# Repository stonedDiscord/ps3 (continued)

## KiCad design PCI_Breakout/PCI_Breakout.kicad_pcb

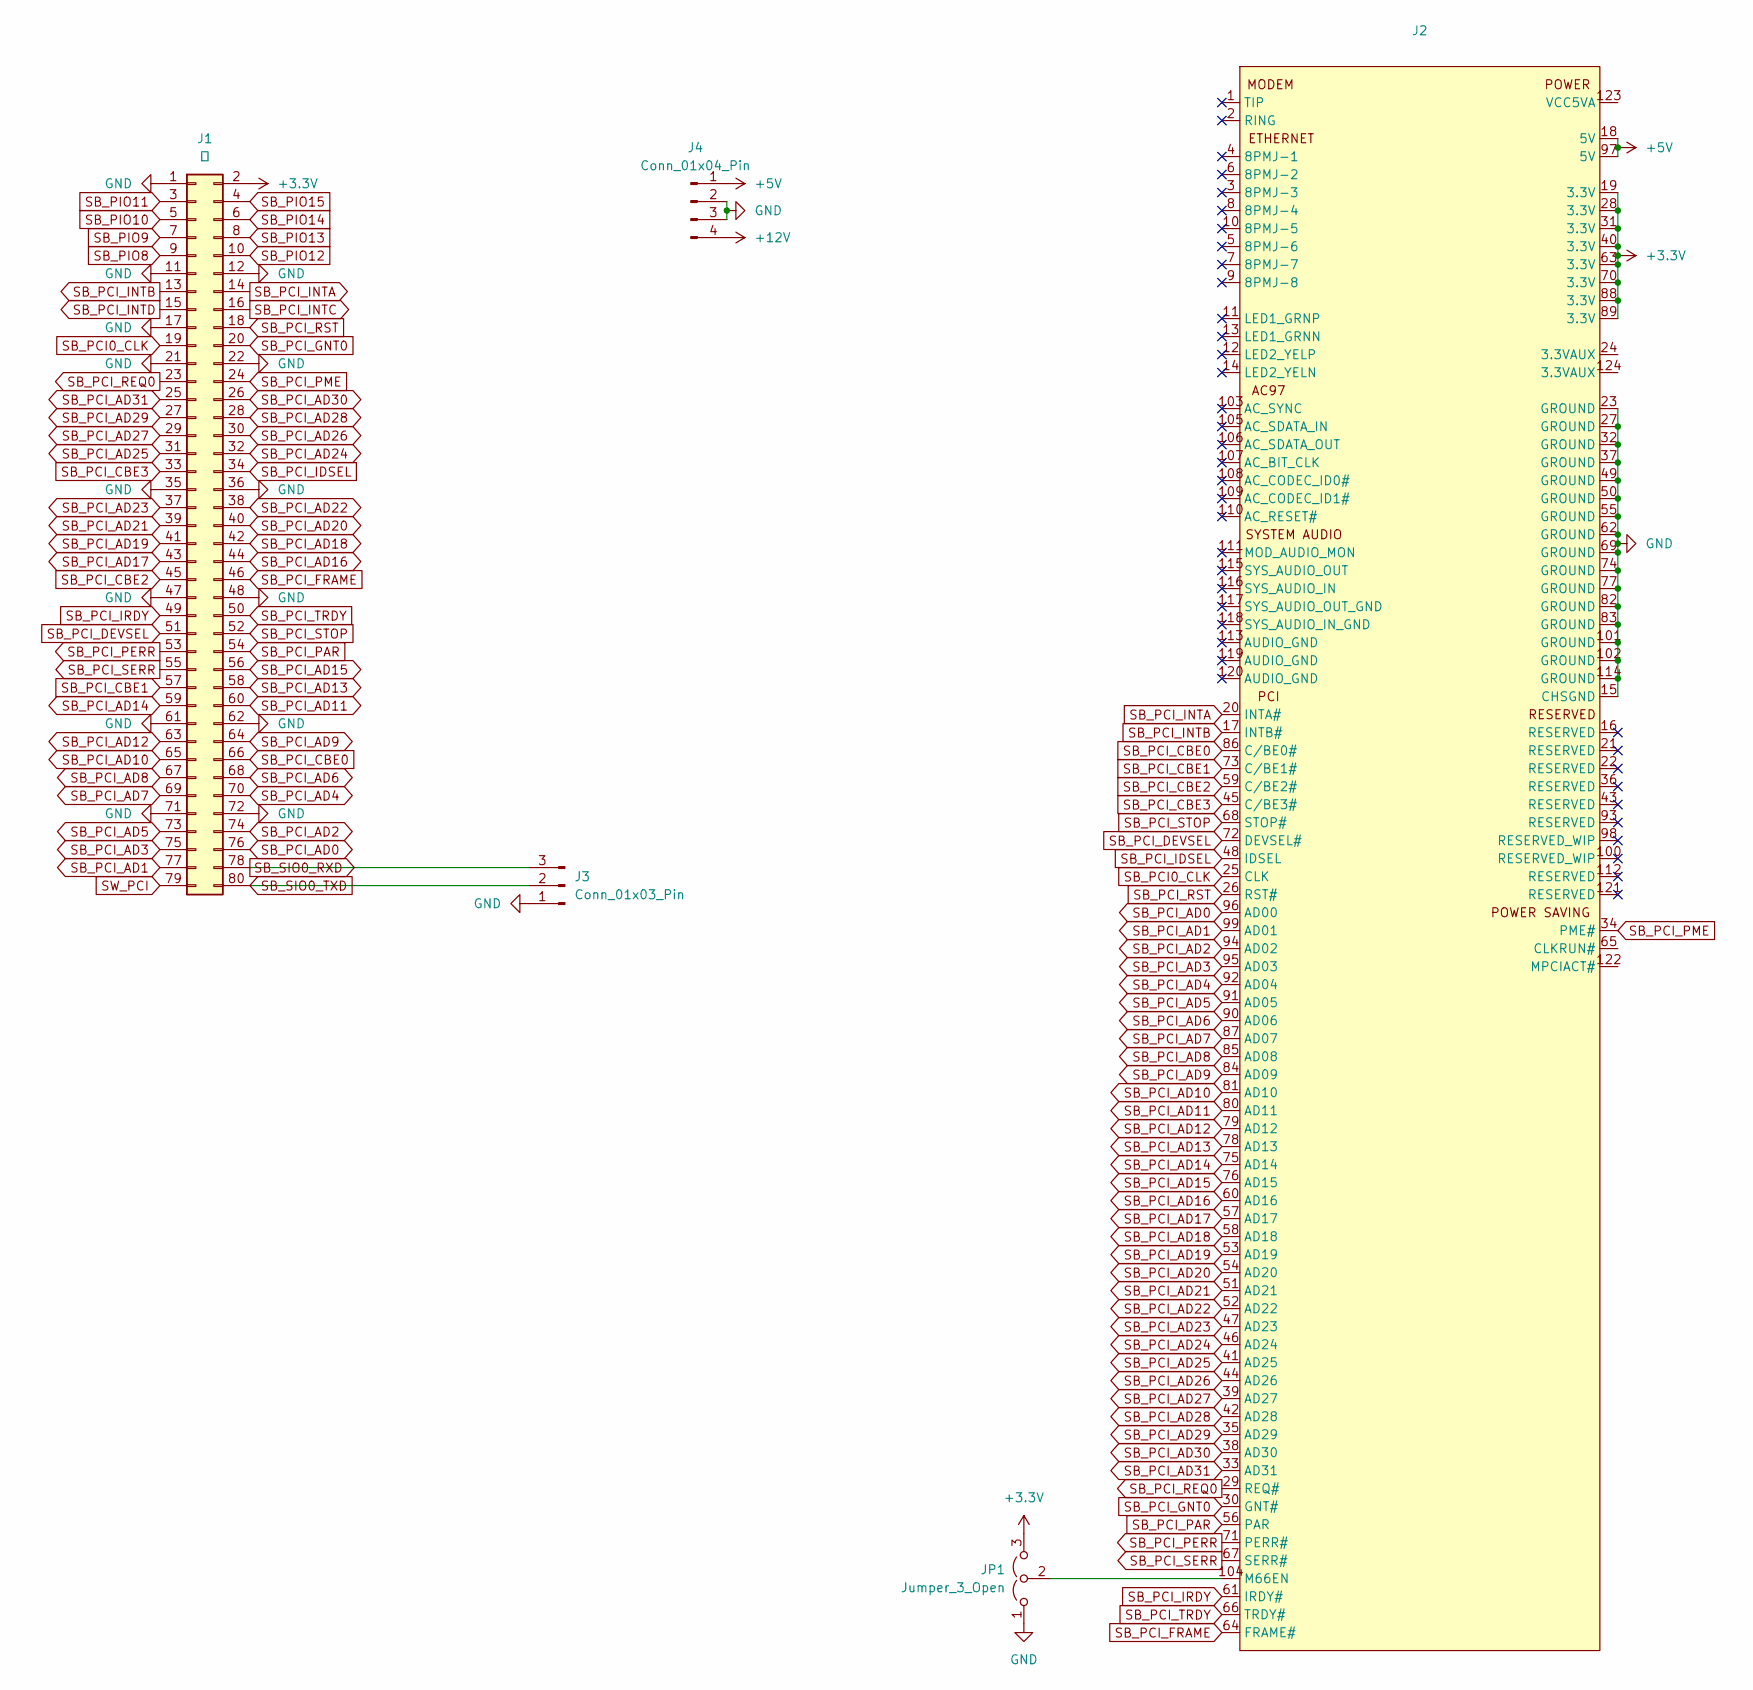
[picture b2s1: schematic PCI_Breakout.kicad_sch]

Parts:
J1: 凹; Molex_SlimStack_55560-0801_2x40_P0.50mm_Vertical
J2: 114B-40B00-R02
J3: Conn_01x03_Pin; PinHeader_1x03_P2.54mm_Vertical
J4: Conn_01x04_Pin; PinHeader_1x04_P2.54mm_Horizontal
JP1: Jumper_3_Open; SolderJumper-3_P2.0mm_Open_TrianglePad1.0x1.5mm

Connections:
+3.3V: J1.2, J2.19 (3.3V), J2.28 (3.3V), J2.31 (3.3V), J2.40 (3.3V), J2.63 (3.3V), J2.70 (3.3V), J2.88 (3.3V), J2.89 (3.3V), JP1.3 (B)
+5V: J2.18 (5V), J2.97 (5V), J4.1
+12V: J4.4
GND: J1.1, J1.11, J1.12, J1.17, J1.21, J1.22, J1.35, J1.36, J1.47, J1.48, J1.61, J1.62, J1.71, J1.72, J2.15 (CHSGND), J2.23 (GROUND), J2.27 (GROUND), J2.32 (GROUND), J2.37 (GROUND), J2.49 (GROUND), J2.50 (GROUND), J2.55 (GROUND), J2.62 (GROUND), J2.69 (GROUND), J2.74 (GROUND), J2.77 (GROUND), J2.82 (GROUND), J2.83 (GROUND), J2.101 (GROUND), J2.102 (GROUND), J2.114 (GROUND), J3.1, J4.2, J4.3, JP1.1 (A)
unnamed: J2.104 (M66EN), JP1.2 (C)
SB_PCI0_CLK: J1.19, J2.25 (CLK)
SB_PCI_AD0: J1.76, J2.96 (AD00)
SB_PCI_AD1: J1.77, J2.99 (AD01)
SB_PCI_AD2: J1.74, J2.94 (AD02)
SB_PCI_AD3: J1.75, J2.95 (AD03)
SB_PCI_AD4: J1.70, J2.92 (AD04)
SB_PCI_AD5: J1.73, J2.91 (AD05)
SB_PCI_AD6: J1.68, J2.90 (AD06)
SB_PCI_AD7: J1.69, J2.87 (AD07)
SB_PCI_AD8: J1.67, J2.85 (AD08)
SB_PCI_AD9: J1.64, J2.84 (AD09)
SB_PCI_AD10: J1.65, J2.81 (AD10)
SB_PCI_AD11: J1.60, J2.80 (AD11)
SB_PCI_AD12: J1.63, J2.79 (AD12)
SB_PCI_AD13: J1.58, J2.78 (AD13)
SB_PCI_AD14: J1.59, J2.75 (AD14)
SB_PCI_AD15: J1.56, J2.76 (AD15)
SB_PCI_AD16: J1.44, J2.60 (AD16)
SB_PCI_AD17: J1.43, J2.57 (AD17)
SB_PCI_AD18: J1.42, J2.58 (AD18)
SB_PCI_AD19: J1.41, J2.53 (AD19)
SB_PCI_AD20: J1.40, J2.54 (AD20)
SB_PCI_AD21: J1.39, J2.51 (AD21)
SB_PCI_AD22: J1.38, J2.52 (AD22)
SB_PCI_AD23: J1.37, J2.47 (AD23)
SB_PCI_AD24: J1.32, J2.46 (AD24)
SB_PCI_AD25: J1.31, J2.41 (AD25)
SB_PCI_AD26: J1.30, J2.44 (AD26)
SB_PCI_AD27: J1.29, J2.39 (AD27)
SB_PCI_AD28: J1.28, J2.42 (AD28)
SB_PCI_AD29: J1.27, J2.35 (AD29)
SB_PCI_AD30: J1.26, J2.38 (AD30)
SB_PCI_AD31: J1.25, J2.33 (AD31)
SB_PCI_CBE0: J1.66, J2.86 (C/BE0#)
SB_PCI_CBE1: J1.57, J2.73 (C/BE1#)
SB_PCI_CBE2: J1.45, J2.59 (C/BE2#)
SB_PCI_CBE3: J1.33, J2.45 (C/BE3#)
SB_PCI_DEVSEL: J1.51, J2.72 (DEVSEL#)
SB_PCI_FRAME: J1.46, J2.64 (FRAME#)
SB_PCI_GNT0: J1.20, J2.30 (GNT#)
SB_PCI_IDSEL: J1.34, J2.48 (IDSEL)
SB_PCI_INTA: J1.14, J2.20 (INTA#)
SB_PCI_INTB: J1.13, J2.17 (INTB#)
SB_PCI_INTC: J1.16
SB_PCI_INTD: J1.15
SB_PCI_IRDY: J1.49, J2.61 (IRDY#)
SB_PCI_PAR: J1.54, J2.56 (PAR)
SB_PCI_PERR: J1.53, J2.71 (PERR#)
SB_PCI_PME: J1.24, J2.34 (PME#)
SB_PCI_REQ0: J1.23, J2.29 (REQ#)
SB_PCI_RST: J1.18, J2.26 (RST#)
SB_PCI_SERR: J1.55, J2.67 (SERR#)
SB_PCI_STOP: J1.52, J2.68 (STOP#)
SB_PCI_TRDY: J1.50, J2.66 (TRDY#)
SB_PIO8: J1.9
SB_PIO9: J1.7
SB_PIO10: J1.5
SB_PIO11: J1.3
SB_PIO12: J1.10
SB_PIO13: J1.8
SB_PIO14: J1.6
SB_PIO15: J1.4
SB_SIO0_RXD: J1.78, J3.3
SB_SIO0_TXD: J1.80, J3.2
SW_PCI: J1.79

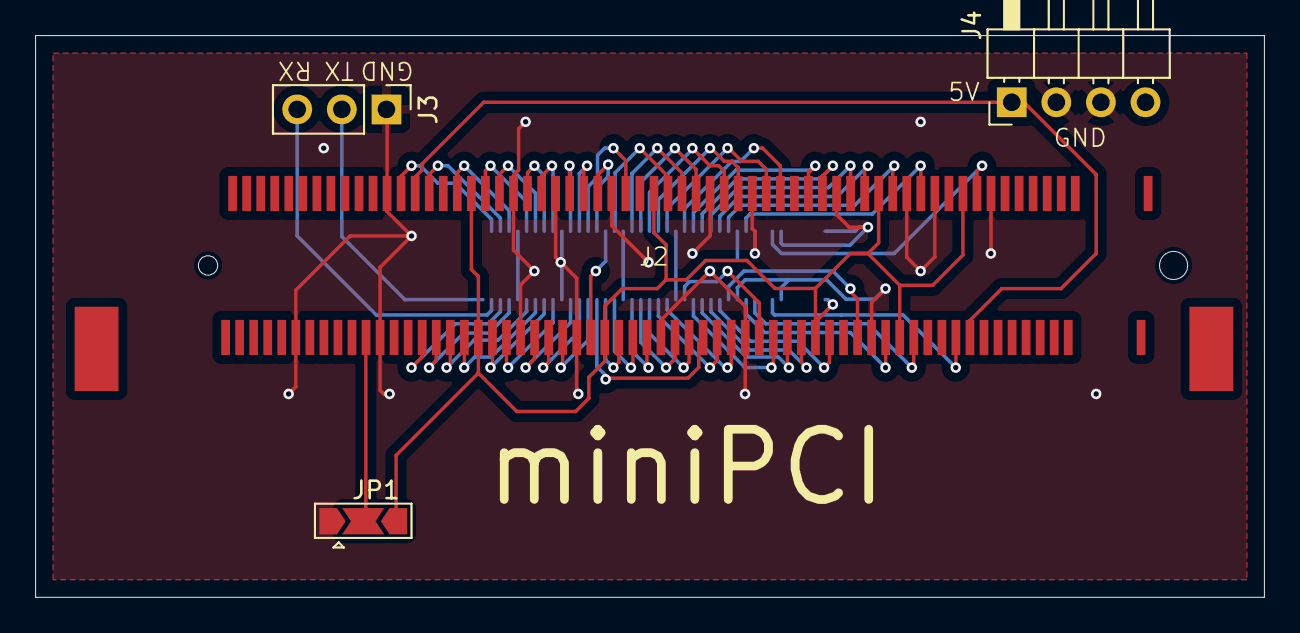
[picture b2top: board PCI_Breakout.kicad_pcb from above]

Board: 2 copper layers, 70.0 x 32.0 mm, 5 parts (1 on the bottom side), 58 nets.

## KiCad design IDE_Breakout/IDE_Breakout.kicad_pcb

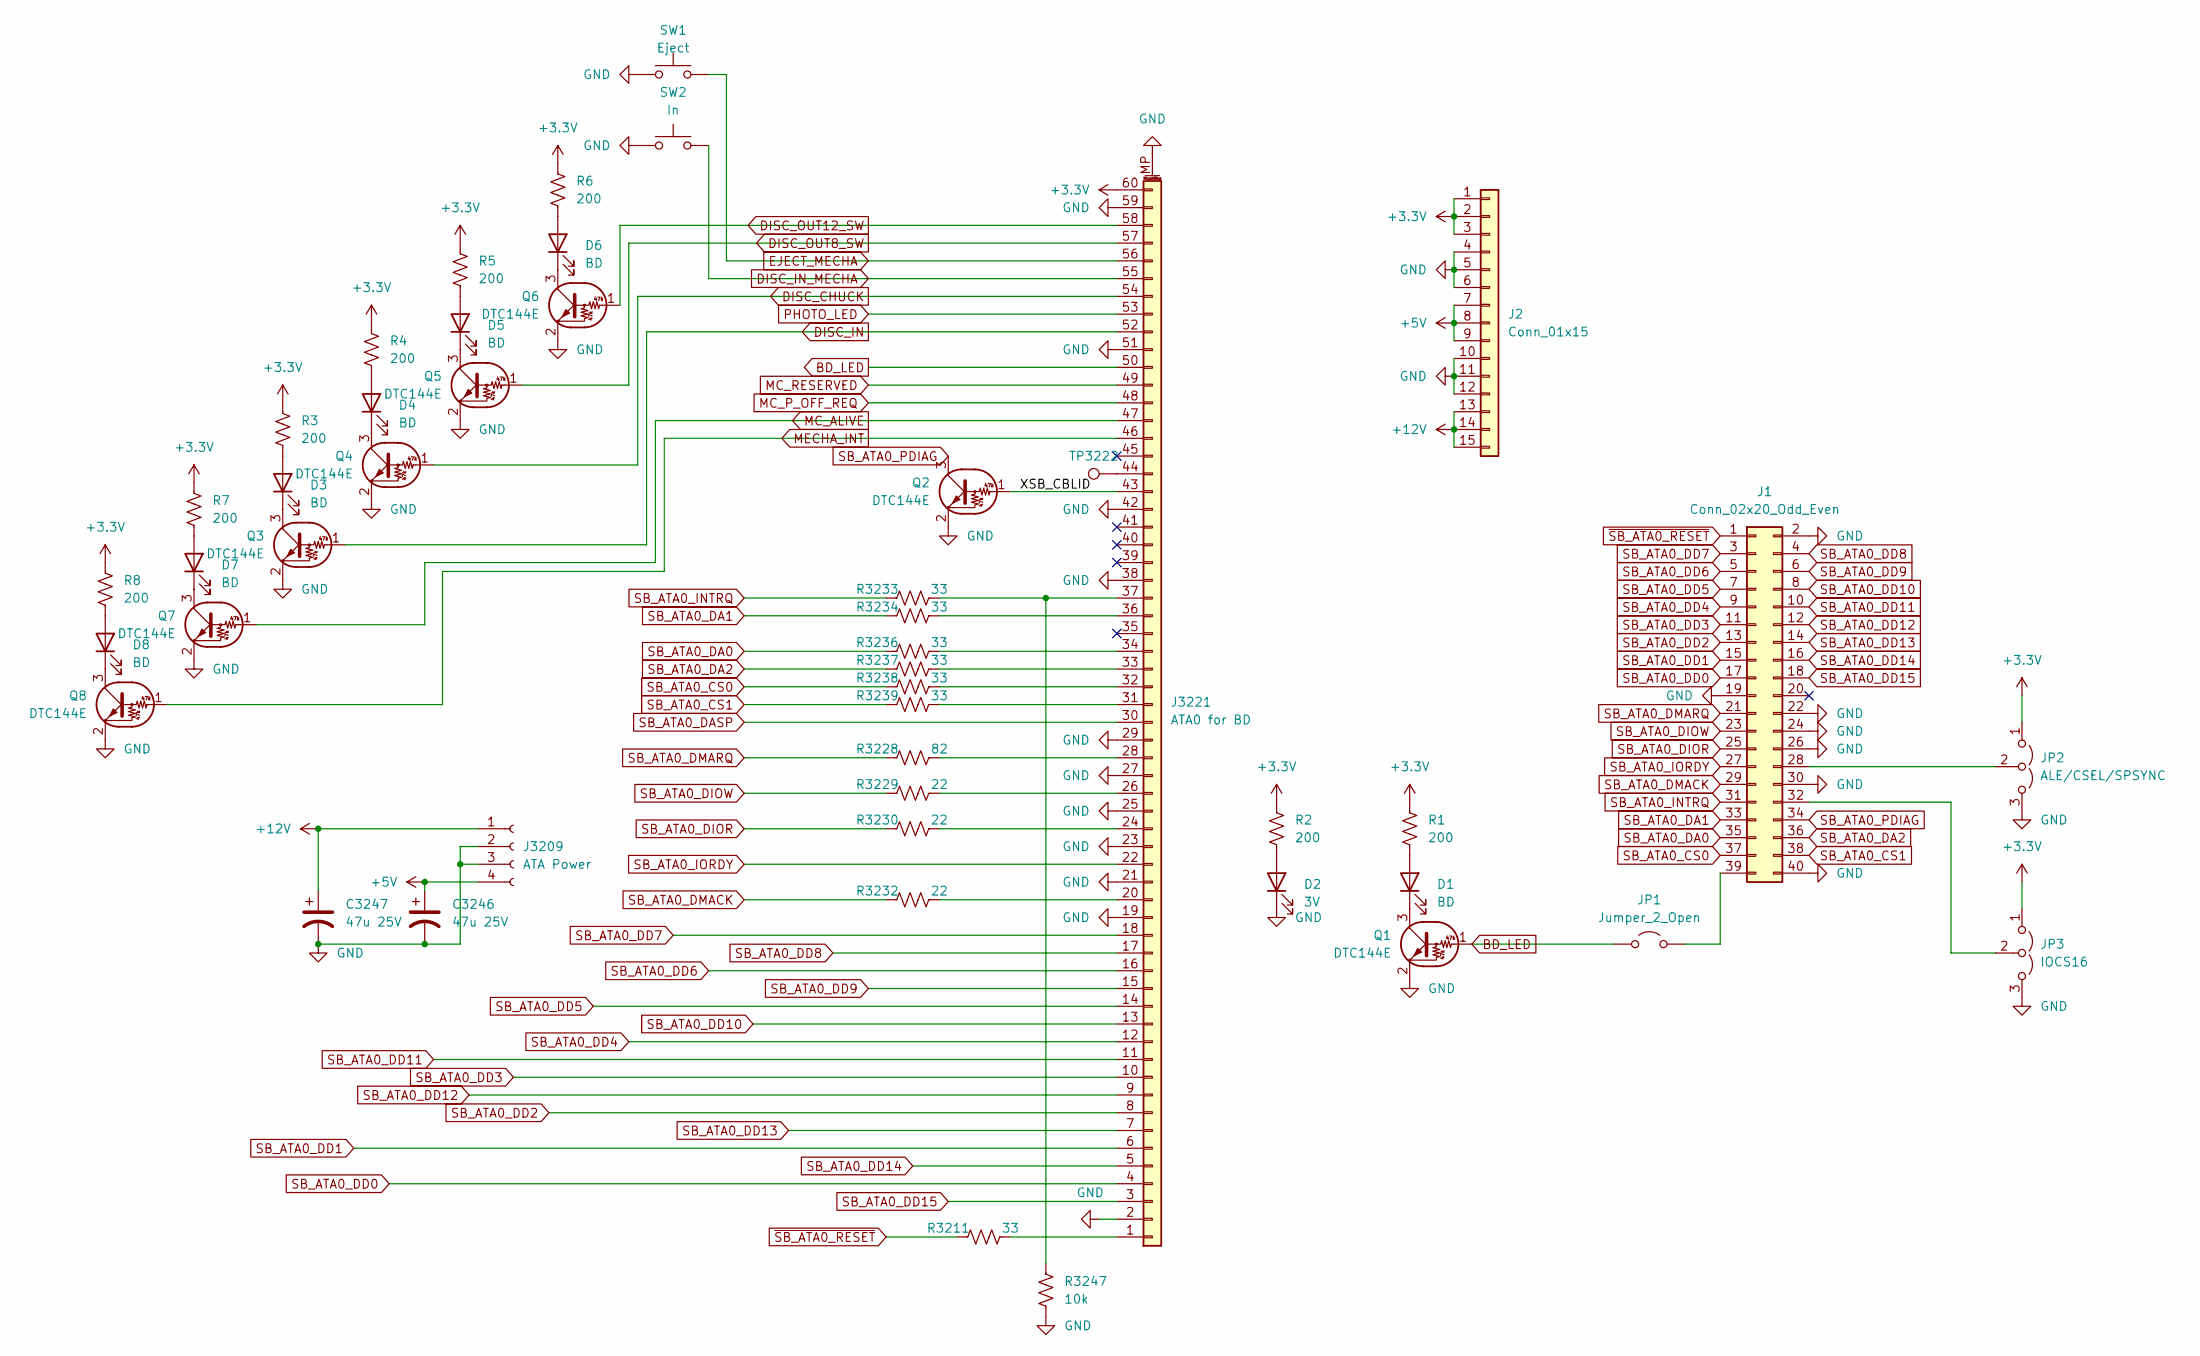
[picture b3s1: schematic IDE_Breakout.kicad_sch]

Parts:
C3246: 47u 25V; CP_EIA-3528-15_AVX-H
C3247: 47u 25V; CP_EIA-7132-28_AVX-C
D1, D3, D4, D5, D6, D7, D8: BD; LED_0603_1608Metric
D2: 3V; LED_0603_1608Metric
J1: Conn_02x20_Odd_Even; IDC-Header_2x20_P2.54mm_Horizontal
J2: Conn_01x15; SATA_Power
J3209: ATA Power; JST_PH_B4B-PH-SM4-TB_1x04-1MP_P2.00mm_Vertical
J3221: ATA0 for BD; Hirose_FH12-60S
JP1: Jumper_2_Open; SolderJumper-2_P1.3mm_Open_TrianglePad1.0x1.5mm
JP2: ALE/CSEL/SPSYNC; SolderJumper-3_P2.0mm_Open_TrianglePad1.0x1.5mm
JP3: IOCS16; SolderJumper-3_P2.0mm_Open_TrianglePad1.0x1.5mm
Q1, Q2, Q3, Q4, Q5, Q6, Q7, Q8: DTC144E; SOT-23
R1, R2, R3, R4, R5, R6, R7, R8: 200; R_0603_1608Metric
R3211, R3233, R3234, R3236, R3237, R3238, R3239: 33; R_0603_1608Metric
R3228: 82; R_0603_1608Metric
R3229, R3230, R3232: 22; R_0603_1608Metric
R3247: 10k; R_0603_1608Metric
SW1: Eject; SW_SPST_PTS647_Sx38
SW2: In; SW_SPST_PTS647_Sx38
TP3222: TestPoint; TestPoint_Pad_1.0x1.0mm

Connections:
+3.3V: J2.1, J2.2, J2.3, J3221.60, JP2.1 (A), JP3.1 (A), R1.1, R2.1, R3.1, R4.1, R5.1, R6.1, R7.1, R8.1
+5V: C3246.1, J2.7, J2.8, J2.9, J3209.4
+12V: C3247.1, J2.13, J2.14, J2.15, J3209.1
/XSB_CBLID: J3221.43, Q2.1 (B)
BD_LED: J3221.50, JP1.1 (A), Q1.1 (B)
DISC_CHUCK: J3221.54, Q4.1 (B)
DISC_IN: J3221.52, Q3.1 (B)
DISC_IN_MECHA: J3221.55, SW2.2
DISC_OUT8_SW: J3221.57, Q5.1 (B)
DISC_OUT12_SW: J3221.58, Q6.1 (B)
EJECT_MECHA: J3221.56, SW1.2
GND: C3246.2, C3247.2, D2.1 (K), J1.2, J1.19, J1.22, J1.24, J1.26, J1.30, J1.40, J2.4, J2.5, J2.6, J2.10, J2.11, J2.12, J3209.2, J3209.3, J3221.2, J3221.19, J3221.21, J3221.23, J3221.25, J3221.27, J3221.29, J3221.38, J3221.42, J3221.51, J3221.59, J3221.MP (MountPin), JP2.3 (B), JP3.3 (B), Q1.2 (E), Q2.2 (E), Q3.2 (E), Q4.2 (E), Q5.2 (E), Q6.2 (E), Q7.2 (E), Q8.2 (E), R3247.2, SW1.1, SW2.1
MC_ALIVE: J3221.47, Q7.1 (B)
MC_P_OFF_REQ: J3221.48
MC_RESERVED: J3221.49
MECHA_INT: J3221.46, Q8.1 (B)
unnamed: D1.2 (A), R1.2
unnamed: D1.1 (K), Q1.3 (C)
unnamed: D2.2 (A), R2.2
unnamed: D3.2 (A), R3.2
unnamed: D3.1 (K), Q3.3 (C)
unnamed: D4.2 (A), R4.2
unnamed: D4.1 (K), Q4.3 (C)
unnamed: D5.2 (A), R5.2
unnamed: D5.1 (K), Q5.3 (C)
unnamed: D6.2 (A), R6.2
unnamed: D6.1 (K), Q6.3 (C)
unnamed: D7.2 (A), R7.2
unnamed: D7.1 (K), Q7.3 (C)
unnamed: D8.2 (A), R8.2
unnamed: D8.1 (K), Q8.3 (C)
unnamed: J1.28, JP2.2 (C)
unnamed: J1.32, JP3.2 (C)
unnamed: J1.39, JP1.2 (B)
unnamed: J3221.1, R3211.2
unnamed: J3221.20, R3232.2
unnamed: J3221.24, R3230.2
unnamed: J3221.26, R3229.2
unnamed: J3221.28, R3228.2
unnamed: J3221.31, R3239.2
unnamed: J3221.32, R3238.2
unnamed: J3221.33, R3237.2
unnamed: J3221.34, R3236.2
unnamed: J3221.36, R3234.2
unnamed: J3221.37, R3233.2, R3247.1
unnamed: J3221.44, TP3222.1
PHOTO_LED: J3221.53
SB_ATA0_CS0: J1.37, R3238.1
SB_ATA0_CS1: J1.38, R3239.1
SB_ATA0_DA0: J1.35, R3236.1
SB_ATA0_DA1: J1.33, R3234.1
SB_ATA0_DA2: J1.36, R3237.1
SB_ATA0_DASP: J3221.30
SB_ATA0_DD0: J1.17, J3221.4
SB_ATA0_DD1: J1.15, J3221.6
SB_ATA0_DD2: J1.13, J3221.8
SB_ATA0_DD3: J1.11, J3221.10
SB_ATA0_DD4: J1.9, J3221.12
SB_ATA0_DD5: J1.7, J3221.14
SB_ATA0_DD6: J1.5, J3221.16
SB_ATA0_DD7: J1.3, J3221.18
SB_ATA0_DD8: J1.4, J3221.17
SB_ATA0_DD9: J1.6, J3221.15
SB_ATA0_DD10: J1.8, J3221.13
SB_ATA0_DD11: J1.10, J3221.11
SB_ATA0_DD12: J1.12, J3221.9
SB_ATA0_DD13: J1.14, J3221.7
SB_ATA0_DD14: J1.16, J3221.5
SB_ATA0_DD15: J1.18, J3221.3
SB_ATA0_DIOR: J1.25, R3230.1
SB_ATA0_DIOW: J1.23, R3229.1
SB_ATA0_DMACK: J1.29, R3232.1
SB_ATA0_DMARQ: J1.21, R3228.1
SB_ATA0_INTRQ: J1.31, R3233.1
SB_ATA0_IORDY: J1.27, J3221.22
SB_ATA0_PDIAG: J1.34, Q2.3 (C)
~SB_ATA0_RESET: J1.1, R3211.1

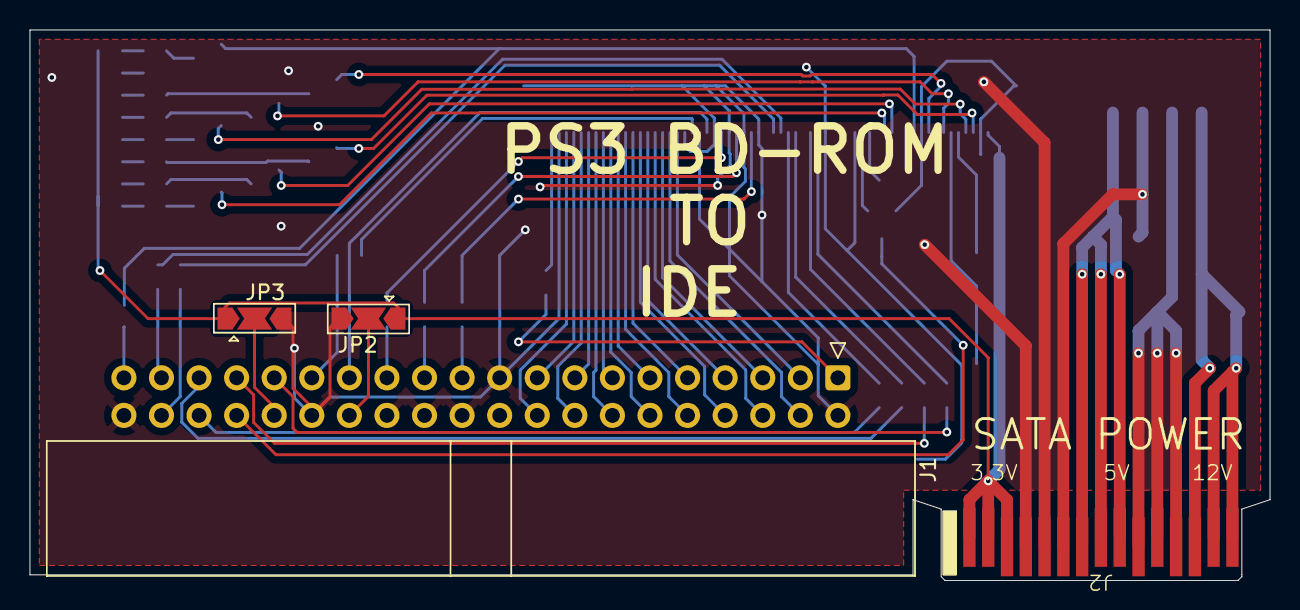
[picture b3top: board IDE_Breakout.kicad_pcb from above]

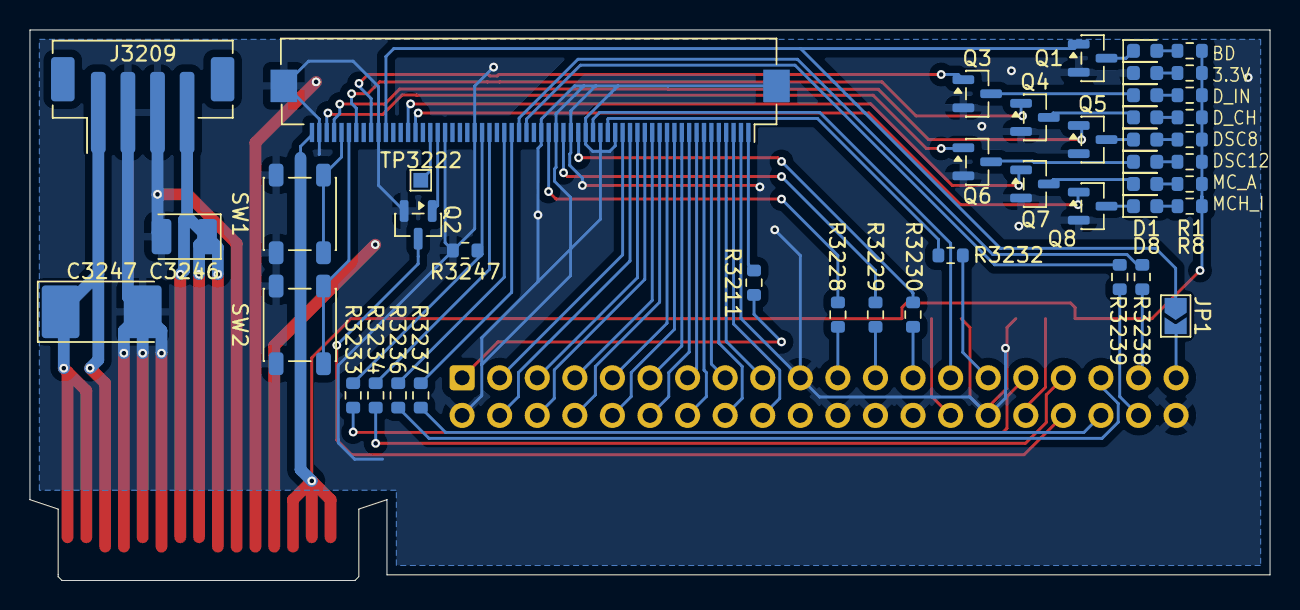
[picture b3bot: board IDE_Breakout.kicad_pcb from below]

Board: 2 copper layers, 83.8 x 37.2 mm, 48 parts (44 on the bottom side), 73 nets.

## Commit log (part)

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2024-06-19 flip ram
2024-06-19 add ram
2024-06-20 new footprints and symbols
2024-06-21 flash
2024-06-21 ncp511 that i ended up scrapping
2024-06-27 starship
2024-07-09 sheets
2024-08-28 fix Sil9132 symbol
2024-08-29 added hdmi and jtag
2024-08-29 scans
2024-08-30 wip eegs
2024-08-31 eegs dc
2024-09-02 add some stupid n channel mosfet
2024-09-04 ethernet
2024-09-12 row c and d
2024-09-16 sata
2024-09-16 board
2024-09-17 southbridge
2024-09-26 bridge sif
2024-09-27 finish SB symbol
2024-09-30 hd sb
2025-03-15 seperate out
2025-03-16 update to 9
2025-04-21 another ics
2025-05-02 linguist override
2025-06-25 footprints
2025-11-02 add cell
2025-11-02 mini pci breakout
2025-11-02 more pci pins
2025-11-02 kicad update
2025-11-03 forgot v
2025-11-03 cpu file
2025-11-09 bdrom ide
2025-11-09 flowchart
2025-11-09 crystal
2025-11-09 wireless
2025-11-09 cell
2025-11-09 power
2025-11-09 hdmi diodes
2025-11-09 new sheets
2025-11-13 ide breakout prod
2025-11-13 coil
2025-11-13 sata crystal
2025-11-14 chris proad
2025-11-14 power in
2025-11-14 pcb update
2025-11-15 rsx pins
2025-11-15 rsx t
2025-11-15 rename symbols
2025-11-15 sb gnd
2025-11-15 extra pins
2025-11-15 rsx vo
2025-11-15 PCIe
2025-11-16 switching regulator
2025-11-16 temp sensor and clock
2025-11-16 pst36
2025-11-16 3d models
2025-11-16 dumb numbers
2025-11-16 optical out
2025-11-16 regulator
2025-11-16 filters
2025-11-16 powea
2025-11-16 inductor
2025-11-17 tx led
2025-11-17 wireless reset
2025-11-19 msop
2025-11-19 ram lines
2025-11-19 ramm
2025-11-20 ram symbol
2025-11-20 cpu pins
2025-11-21 button connector
2025-11-28 power flags
2025-11-28 av move
2025-12-27 caps
2025-12-30 current sense
2025-12-30 lanes
2025-12-30 pid in
2025-12-30 pid pinout
2025-12-30 reset
2025-12-30 voltage symbols
2026-01-20 rsx symbol done
2026-01-21 fix 1 rsx pin
